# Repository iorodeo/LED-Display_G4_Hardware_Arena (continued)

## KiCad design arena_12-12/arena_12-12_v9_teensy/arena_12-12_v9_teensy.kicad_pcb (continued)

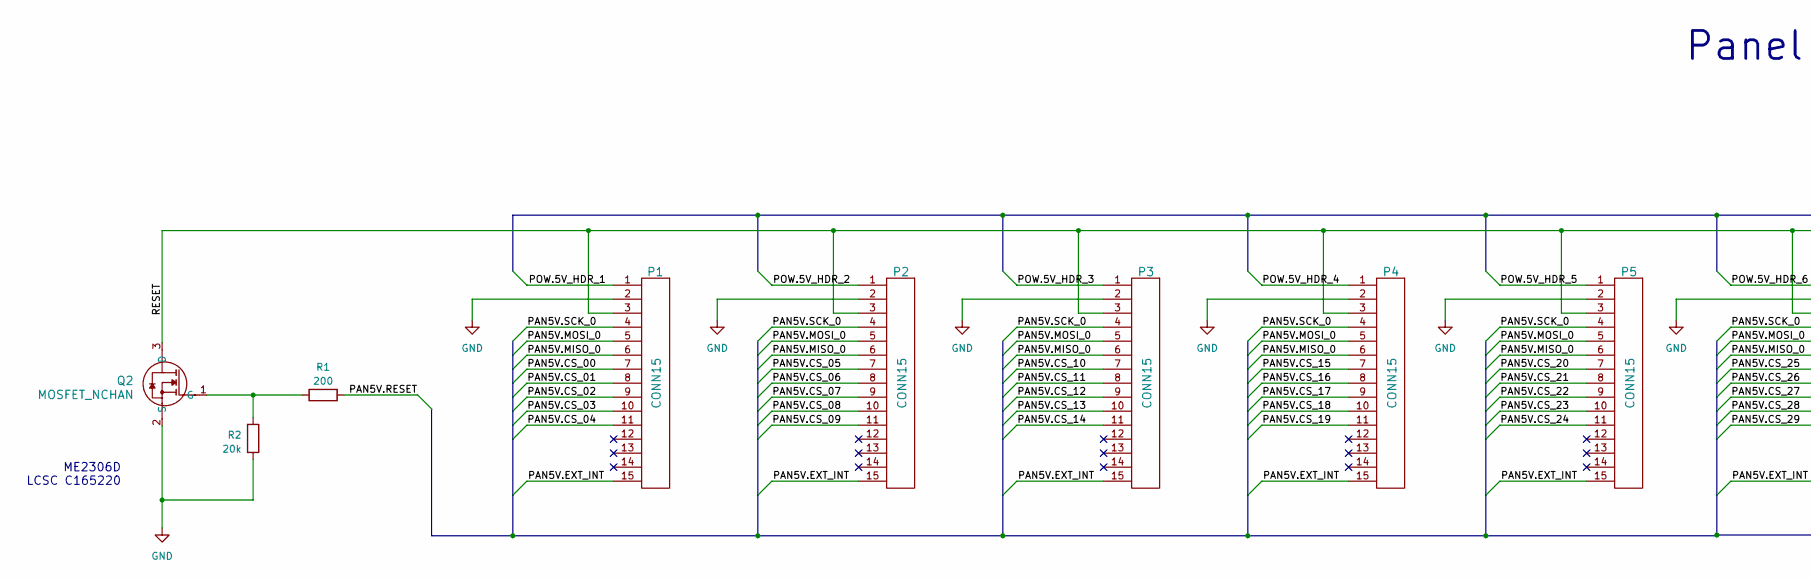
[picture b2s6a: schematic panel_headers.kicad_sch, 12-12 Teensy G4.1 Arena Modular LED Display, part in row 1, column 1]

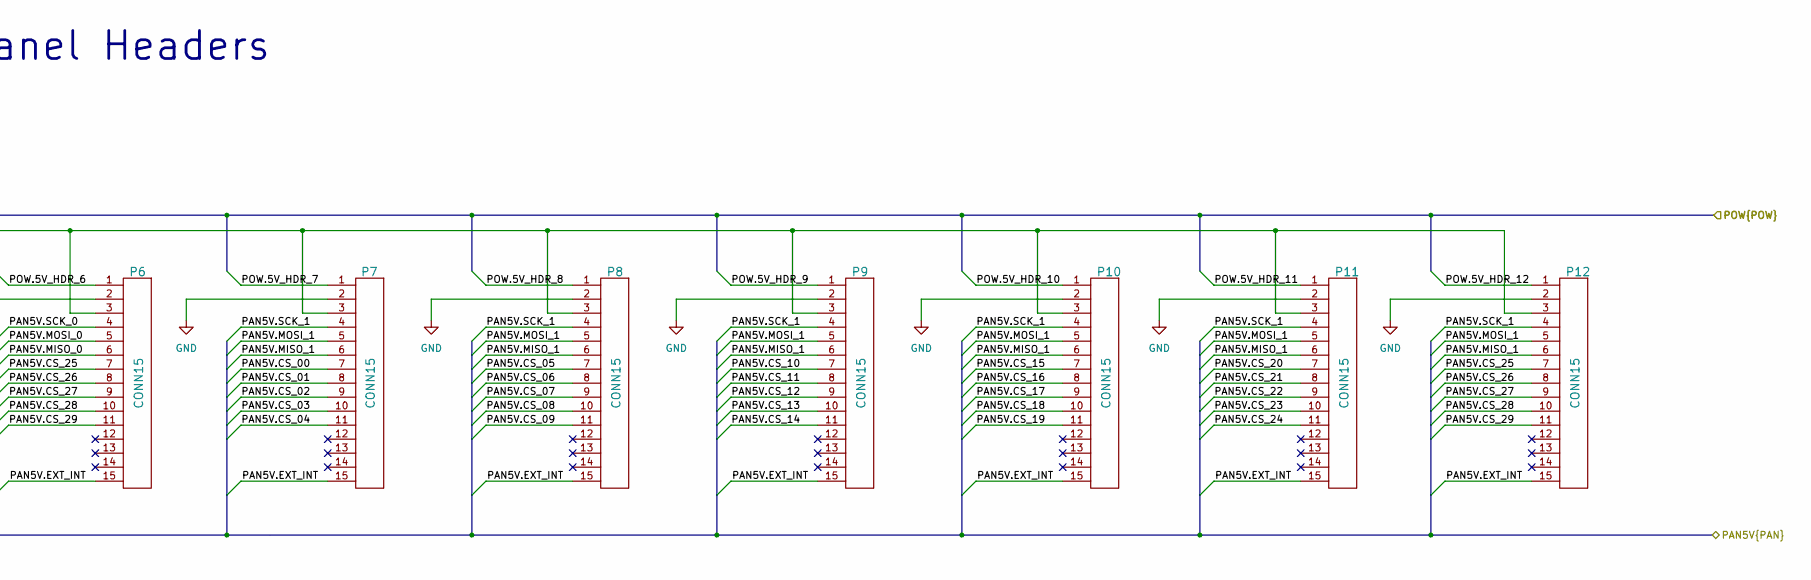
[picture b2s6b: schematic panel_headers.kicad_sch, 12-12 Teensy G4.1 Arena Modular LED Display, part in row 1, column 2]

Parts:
P1, P2, P3, P4, P5, P6, P7, P8, P9, P10, P11, P12: CONN15; HEADER_TOP; MPN PPPC151LFBN-RC; DigiKey PN S7048-ND
Q2: MOSFET_NCHAN; SOT-23-3; MPN ME2306D; LCSC PN C165220
R1: 200; R_0805_2012Metric; MPN 0805W8F2000T5E; LCSC PN C17540
R2: 20k; R_0805_2012Metric; MPN 0805W8F2002T5E; LCSC PN C4328

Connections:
/Level Shifters/PAN5V.CS_00: P1.7, P7.7; also elsewhere on the board
/Level Shifters/PAN5V.CS_01: P1.8, P7.8; also elsewhere on the board
/Level Shifters/PAN5V.CS_02: P1.9, P7.9; also elsewhere on the board
/Level Shifters/PAN5V.CS_03: P1.10, P7.10; also elsewhere on the board
/Level Shifters/PAN5V.CS_04: P1.11, P7.11; also elsewhere on the board
/Level Shifters/PAN5V.CS_05: P2.7, P8.7; also elsewhere on the board
/Level Shifters/PAN5V.CS_06: P2.8, P8.8; also elsewhere on the board
/Level Shifters/PAN5V.CS_07: P2.9, P8.9; also elsewhere on the board
/Level Shifters/PAN5V.CS_08: P2.10, P8.10; also elsewhere on the board
/Level Shifters/PAN5V.CS_09: P2.11, P8.11; also elsewhere on the board
/Level Shifters/PAN5V.CS_10: P3.7, P9.7; also elsewhere on the board
/Level Shifters/PAN5V.CS_11: P3.8, P9.8; also elsewhere on the board
/Level Shifters/PAN5V.CS_12: P3.9, P9.9; also elsewhere on the board
/Level Shifters/PAN5V.CS_13: P3.10, P9.10; also elsewhere on the board
/Level Shifters/PAN5V.CS_14: P3.11, P9.11; also elsewhere on the board
/Level Shifters/PAN5V.CS_15: P4.7, P10.7; also elsewhere on the board
/Level Shifters/PAN5V.CS_16: P4.8, P10.8; also elsewhere on the board
/Level Shifters/PAN5V.CS_17: P4.9, P10.9; also elsewhere on the board
/Level Shifters/PAN5V.CS_18: P4.10, P10.10; also elsewhere on the board
/Level Shifters/PAN5V.CS_19: P4.11, P10.11; also elsewhere on the board
/Level Shifters/PAN5V.CS_20: P5.7, P11.7; also elsewhere on the board
/Level Shifters/PAN5V.CS_21: P5.8, P11.8; also elsewhere on the board
/Level Shifters/PAN5V.CS_22: P5.9, P11.9; also elsewhere on the board
/Level Shifters/PAN5V.CS_23: P5.10, P11.10; also elsewhere on the board
/Level Shifters/PAN5V.CS_24: P5.11, P11.11; also elsewhere on the board
/Level Shifters/PAN5V.CS_25: P6.7, P12.7; also elsewhere on the board
/Level Shifters/PAN5V.CS_26: P6.8, P12.8; also elsewhere on the board
/Level Shifters/PAN5V.CS_27: P6.9, P12.9; also elsewhere on the board
/Level Shifters/PAN5V.CS_28: P6.10, P12.10; also elsewhere on the board
/Level Shifters/PAN5V.CS_29: P6.11, P12.11; also elsewhere on the board
/Level Shifters/PAN5V.EXT_INT: P1.15, P2.15, P3.15, P4.15, P5.15, P6.15, P7.15, P8.15, P9.15, P10.15, P11.15, P12.15; also elsewhere on the board
/Level Shifters/PAN5V.MISO_0: P1.6, P2.6, P3.6, P4.6, P5.6, P6.6; also elsewhere on the board
/Level Shifters/PAN5V.MISO_1: P7.6, P8.6, P9.6, P10.6, P11.6, P12.6; also elsewhere on the board
/Level Shifters/PAN5V.MOSI_0: P1.5, P2.5, P3.5, P4.5, P5.5, P6.5; also elsewhere on the board
/Level Shifters/PAN5V.MOSI_1: P7.5, P8.5, P9.5, P10.5, P11.5, P12.5; also elsewhere on the board
/Level Shifters/PAN5V.RESET: R1.2; also elsewhere on the board
/Level Shifters/PAN5V.SCK_0: P1.4, P2.4, P3.4, P4.4, P5.4, P6.4; also elsewhere on the board
/Level Shifters/PAN5V.SCK_1: P7.4, P8.4, P9.4, P10.4, P11.4, P12.4; also elsewhere on the board
/Panel Headers/POW.5V_HDR_1: P1.1; also elsewhere on the board
/Panel Headers/POW.5V_HDR_2: P2.1; also elsewhere on the board
/Panel Headers/POW.5V_HDR_3: P3.1; also elsewhere on the board
/Panel Headers/POW.5V_HDR_4: P4.1; also elsewhere on the board
/Panel Headers/POW.5V_HDR_5: P5.1; also elsewhere on the board
/Panel Headers/POW.5V_HDR_6: P6.1; also elsewhere on the board
/Panel Headers/POW.5V_HDR_7: P7.1; also elsewhere on the board
/Panel Headers/POW.5V_HDR_8: P8.1; also elsewhere on the board
/Panel Headers/POW.5V_HDR_9: P9.1; also elsewhere on the board
/Panel Headers/POW.5V_HDR_10: P10.1; also elsewhere on the board
/Panel Headers/POW.5V_HDR_11: P11.1; also elsewhere on the board
/Panel Headers/POW.5V_HDR_12: P12.1; also elsewhere on the board
/Panel Headers/RESET: P1.3, P2.3, P3.3, P4.3, P5.3, P6.3, P7.3, P8.3, P9.3, P10.3, P11.3, P12.3, Q2.3 (D)
GND: P1.2, P2.2, P3.2, P4.2, P5.2, P6.2, P7.2, P8.2, P9.2, P10.2, P11.2, P12.2, Q2.2 (S), R2.1; also elsewhere on the board
unnamed: Q2.1 (G), R1.1, R2.2

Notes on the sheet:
Panel Headers
ME2306D LCSC C165220

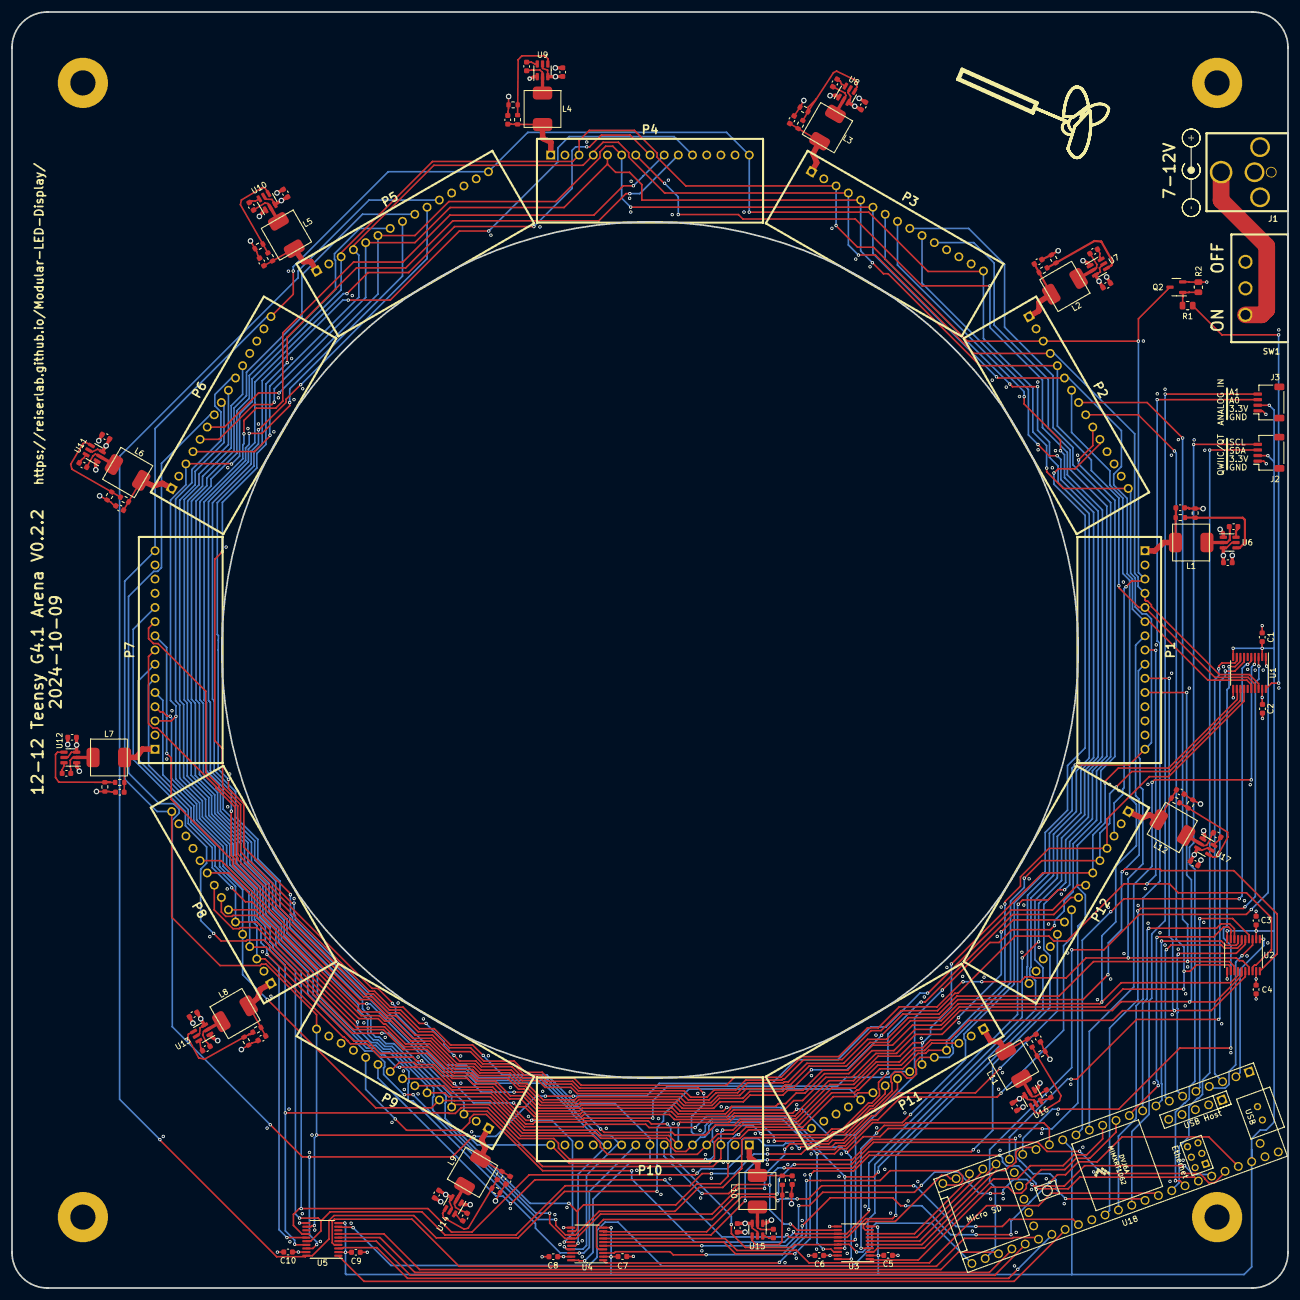
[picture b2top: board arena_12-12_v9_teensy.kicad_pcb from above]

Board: 6 copper layers, 228.6 x 228.6 mm, 123 parts (0 on the bottom side), 135 nets.

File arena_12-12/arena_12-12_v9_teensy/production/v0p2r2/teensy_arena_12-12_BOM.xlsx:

Comment | Designator | Footprint | JLCPCB Part #
0.1uF | C1,C2,C3,C4,C5,C6,C7,C8,C9,C10 | Capacitor_SMD:C_0603_1608Metric | C1591
10uF | C11,C14,C17,C20,C23,C26,C29,C32,C35,C38,C41,C44 | Capacitor_SMD:C_0603_1608Metric | C96446
100nF | C12,C15,C18,C21,C24,C27,C30,C33,C36,C39,C42,C45 | Capacitor_SMD:C_0603_1608Metric | C1591
22uF | C13,C16,C19,C22,C25,C28,C31,C34,C37,C40,C43,C46 | Capacitor_SMD:C_0603_1608Metric | C2762594
Barrel_Jack | J1 | arena_custom:DCJACK_2PIN_HIGHCURRENT | C2928097
Conn_01x04 | J2,J3 | arena_custom:JST_SH_SM04B-SRSS-TB_1x04-1MP_P1.00mm_Horizontal | C145956
3.3uH | L1,L2,L3,L4,L5,L6,L7,L8,L9,L10,L11,L12 | arena_custom:CYA0650_3P3UH | C5189747
CONN15 | P1,P2,P3,P4,P5,P6,P7,P8,P9,P10,P11,P12 | arena_custom:HEADER_TOP | C5210739
MOSFET_NCHAN | Q2 | Package_TO_SOT_SMD:SOT-23-3 | C165220
200 | R1 | Resistor_SMD:R_0805_2012Metric | C17540
20k | R2 | Resistor_SMD:R_0805_2012Metric | C4328
56.2k | R3,R5,R7,R9,R11,R13,R15,R17,R19,R21,R23,R25 | Resistor_SMD:R_0603_1608Metric | C705784
10k | R4,R6,R8,R10,R12,R14,R16,R18,R20,R22,R24,R26 | Resistor_SMD:R_0603_1608Metric | C95204
SW_SPDT | SW1 | arena_custom:slide_switch | C2798743
TXB0108PW | U1,U2,U3,U4,U5 | Package_SO:TSSOP-20_4.4x6.5mm_P0.65mm | C53406
TPS564201DDC | U6,U7,U8,U9,U10,U11,U12,U13,U14,U15,U16,U17 | Package_TO_SOT_SMD:SOT-23-6 | C464812

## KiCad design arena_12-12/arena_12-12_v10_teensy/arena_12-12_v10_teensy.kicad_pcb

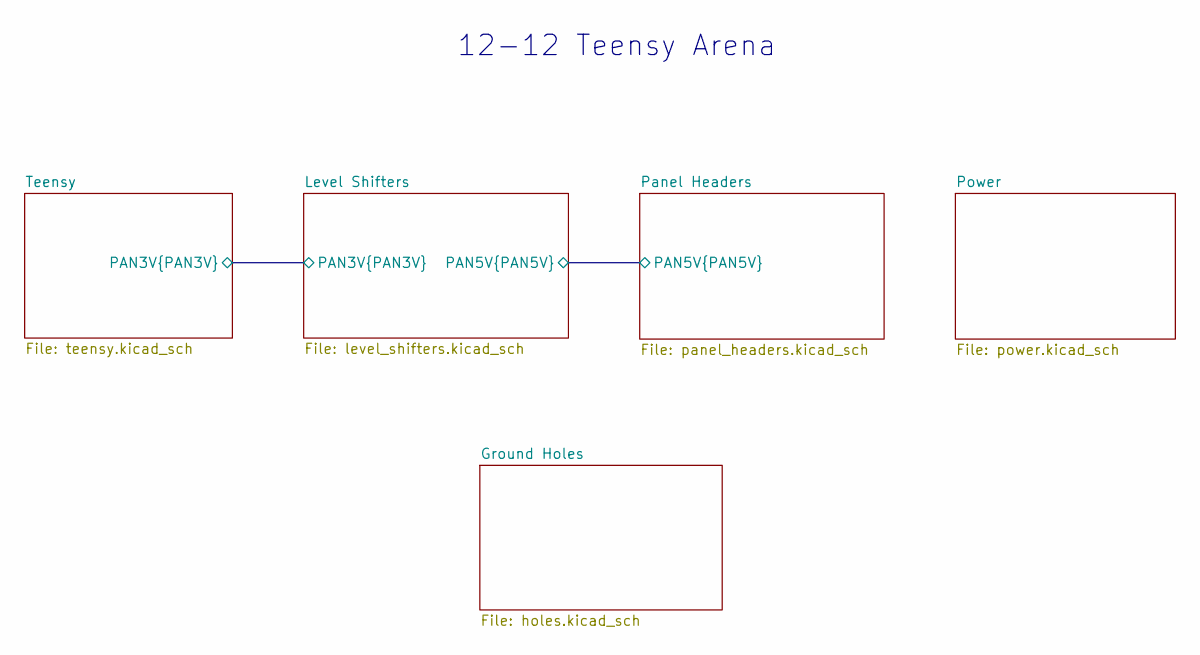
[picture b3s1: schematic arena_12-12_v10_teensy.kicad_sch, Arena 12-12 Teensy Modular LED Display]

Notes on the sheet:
12-12 Teensy Arena
